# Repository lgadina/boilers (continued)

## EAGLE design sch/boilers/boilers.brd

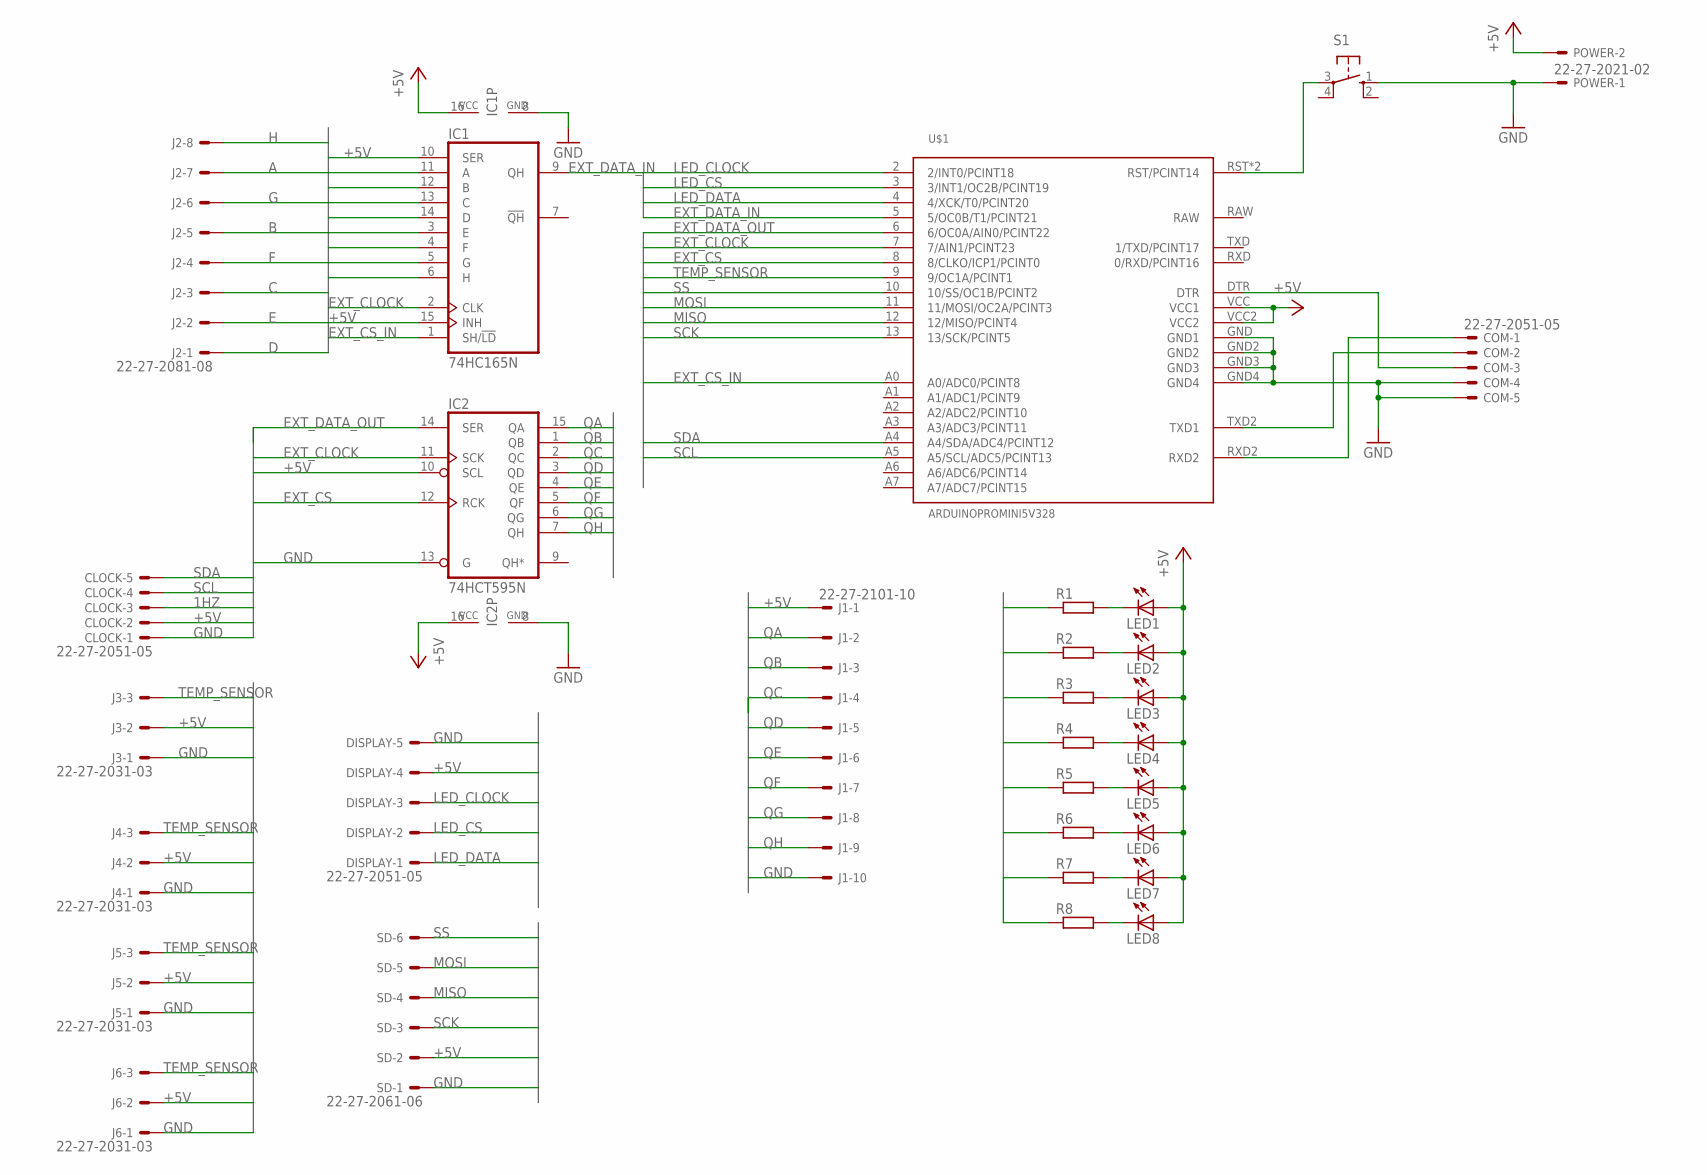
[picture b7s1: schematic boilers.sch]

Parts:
CLOCK: 22-27-2051-05; 6410-05
COM: 22-27-2051-05; 6410-05
DISPLAY: 22-27-2051-05; 6410-05
IC1: 74HC165N; DIL16
IC2: 74HCT595N; DIL16
J1: 22-27-2101-10; 6410-10
J2: 22-27-2081-08; 6410-08
J3, J4, J5, J6: 22-27-2031-03; 6410-03
LED1, LED2, LED3, LED4, LED5, LED6, LED7, LED8: LED5MM
POWER: 22-27-2021-02; 6410-02
R1, R2, R3, R4, R5, R6, R7, R8: R-EU_0207/10; 0207/10
S1: 10-XX; B3F-10XX
SD: 22-27-2061-06; 6410-06
U$1: ARDUINOPROMINI5V328; ARDUINOMINIPRO5V328

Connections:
1HZ: CLOCK.3
+5V: CLOCK.2, DISPLAY.4, IC1.10 (SER), IC1.15 (INH), IC1.16 (VCC), IC2.10 (SCL), IC2.16 (VCC), J1.1, J3.2, J4.2, J5.2, J6.2, LED1.A, LED2.A, LED3.A, LED4.A, LED5.A, LED6.A, LED7.A, LED8.A, POWER.2, SD.2, U$1.VCC (VCC1), U$1.VCC2
A: IC1.11 (A), J2.7
B: IC1.12 (B), J2.5
C: IC1.13 (C), J2.3
D: IC1.14 (D), J2.1
E: IC1.3 (E), J2.2
EXT_CLOCK: IC1.2 (CLK), IC2.11 (SCK), U$1.7 (7/AIN1/PCINT23)
EXT_CS: IC2.12 (RCK), U$1.8 (8/CLKO/ICP1/PCINT0)
EXT_CS_IN: IC1.1 (SH/!LD), U$1.A0 (A0/ADC0/PCINT8)
EXT_DATA_IN: IC1.9 (QH), U$1.5 (5/OC0B/T1/PCINT21)
EXT_DATA_OUT: IC2.14 (SER), U$1.6 (6/OC0A/AIN0/PCINT22)
F: IC1.4 (F), J2.4
G: IC1.5 (G), J2.6
GND: CLOCK.1, COM.4, COM.5, DISPLAY.5, IC1.8 (GND), IC2.8 (GND), IC2.13 (G), J1.10, J3.1, J4.1, J5.1, J6.1, POWER.1, S1.1 (S), SD.1, U$1.GND (GND1), U$1.GND2, U$1.GND3, U$1.GND4
H: IC1.6 (H), J2.8
LED_CLOCK: DISPLAY.3, U$1.2 (2/INT0/PCINT18)
LED_CS: DISPLAY.2, U$1.3 (3/INT1/OC2B/PCINT19)
LED_DATA: DISPLAY.1, U$1.4 (4/XCK/T0/PCINT20)
MISO: SD.4, U$1.12 (12/MISO/PCINT4)
MOSI: SD.5, U$1.11 (11/MOSI/OC2A/PCINT3)
unnamed: COM.1, U$1.RXD2
unnamed: COM.3, U$1.DTR
unnamed: LED1.K (C), R1.2
unnamed: LED2.K (C), R2.2
unnamed: LED3.K (C), R3.2
unnamed: LED4.K (C), R4.2
unnamed: LED5.K (C), R5.2
unnamed: LED6.K (C), R6.2
unnamed: LED7.K (C), R7.2
unnamed: LED8.K (C), R8.2
QA: IC2.15 (QA), J1.2, R1.1
QB: IC2.1 (QB), J1.3, R2.1
QC: IC2.2 (QC), J1.4, R3.1
QD: IC2.3 (QD), J1.5, R4.1
QE: IC2.4 (QE), J1.6, R5.1
QF: IC2.5 (QF), J1.7, R6.1
QG: IC2.6 (QG), J1.8, R7.1
QH: IC2.7 (QH), J1.9, R8.1
RESET: S1.3, U$1.RST (RST/PCINT14), U$1.RST2 (RST/PCINT14)
SCK: SD.3, U$1.13 (13/SCK/PCINT5)
SCL: CLOCK.4, U$1.A5 (A5/SCL/ADC5/PCINT13)
SDA: CLOCK.5, U$1.A4 (A4/SDA/ADC4/PCINT12)
SS: SD.6, U$1.10 (10/SS/OC1B/PCINT2)
TEMP_SENSOR: J3.3, J4.3, J5.3, J6.3, U$1.9 (9/OC1A/PCINT1)
TXD: COM.2, U$1.TXD2 (TXD1)

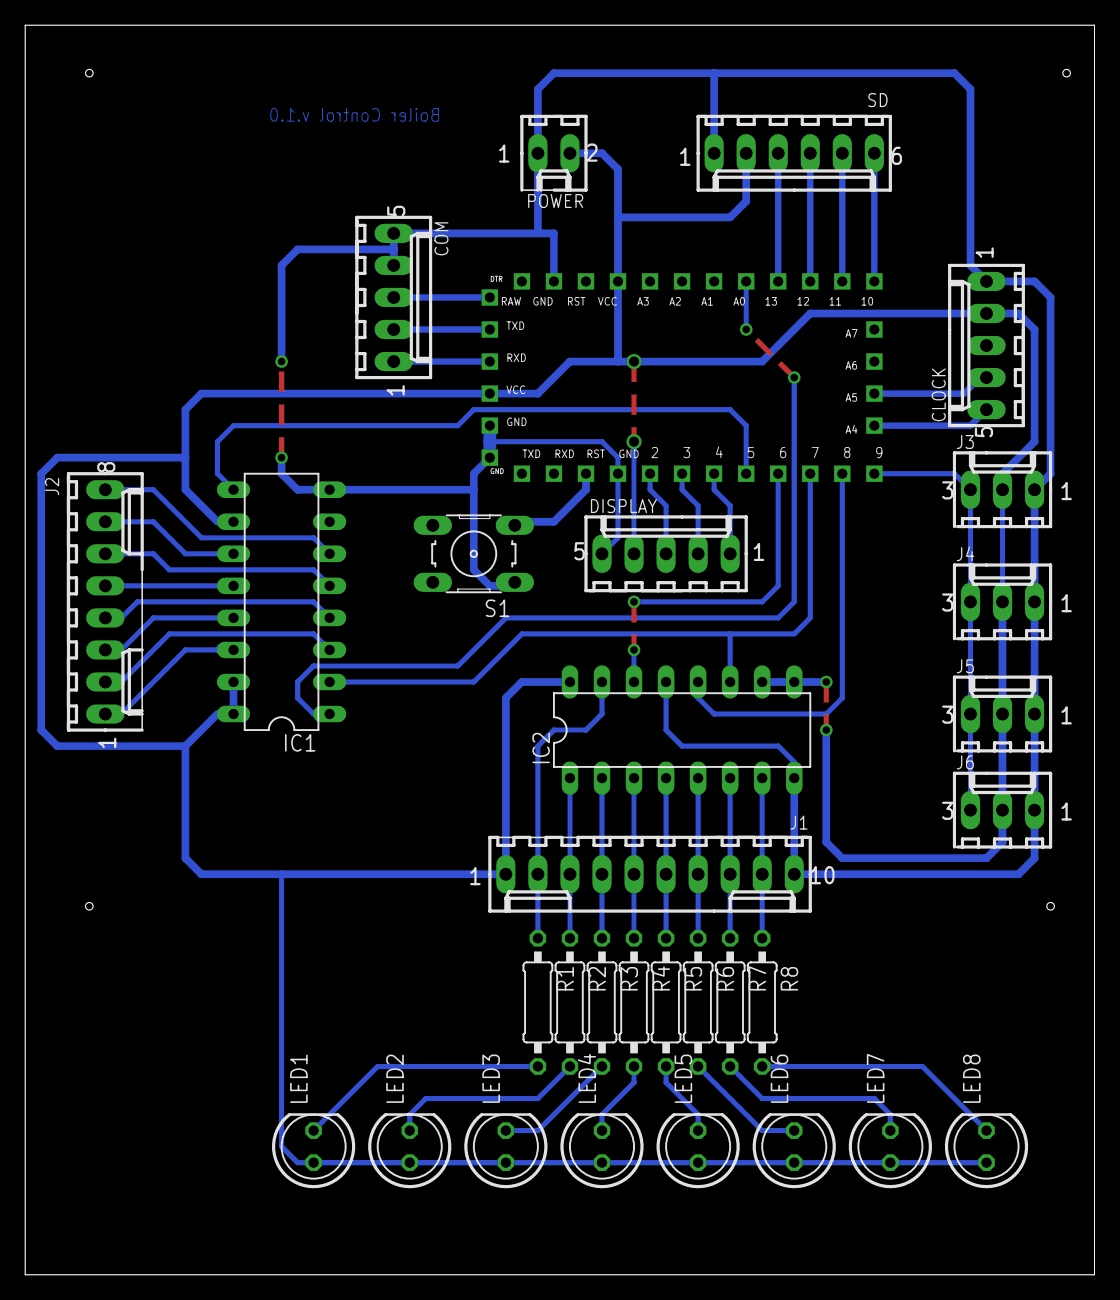
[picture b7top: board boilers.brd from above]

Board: 2 copper layers, 84.8 x 99.1 mm, 31 parts (0 on the bottom side), 45 nets.

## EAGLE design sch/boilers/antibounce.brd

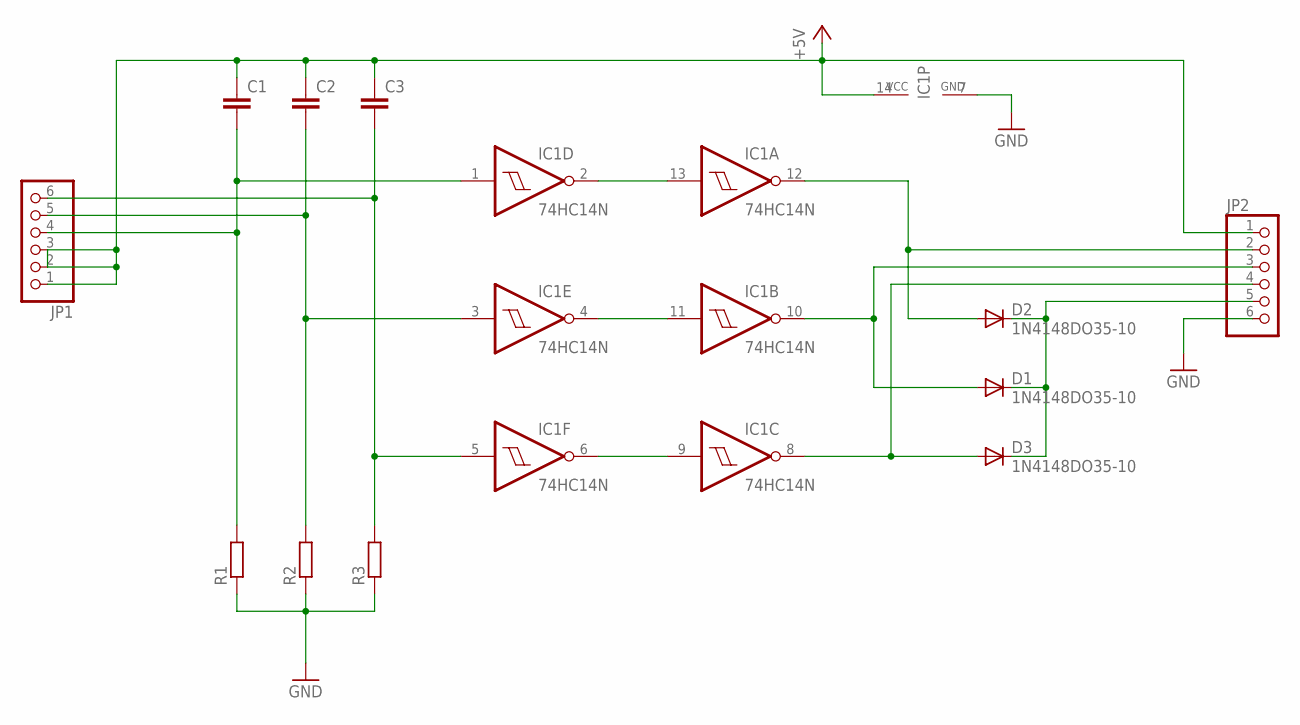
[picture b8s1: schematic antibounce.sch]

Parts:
C1, C2, C3: C-EU050-024X044; C050-024X044
D1, D2, D3: 1N4148DO35-10; DO35-10
IC1: 74HC14N; DIL14
JP1, JP2: PINHD-1X6; 1X06
R1, R2, R3: R-EU_0207/10; 0207/10

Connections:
+5V: C1.1, C2.1, C3.1, IC1.14 (VCC), JP1.1, JP1.2, JP1.3, JP2.1
GND: IC1.7 (GND), JP2.6, R1.1, R2.1, R3.1
unnamed: C1.2, IC1.1 (I), JP1.4, R1.2
unnamed: C2.2, IC1.3 (I), JP1.5, R2.2
unnamed: C3.2, IC1.5 (I), JP1.6, R3.2
unnamed: IC1.2 (O), IC1.13 (I)
unnamed: IC1.6 (O), IC1.9 (I)
unnamed: IC1.4 (O), IC1.11 (I)
unnamed: D2.A, IC1.12 (O), JP2.2
unnamed: D1.C, D2.C, D3.C, JP2.5
unnamed: D1.A, IC1.10 (O), JP2.3
unnamed: D3.A, IC1.8 (O), JP2.4

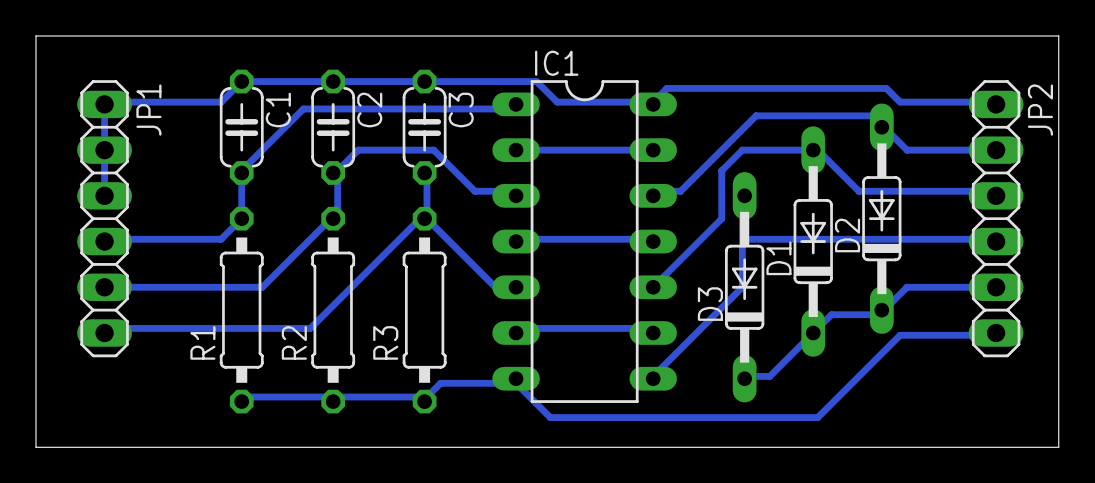
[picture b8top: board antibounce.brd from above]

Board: 2 copper layers, 56.8 x 22.9 mm, 12 parts (0 on the bottom side), 12 nets.

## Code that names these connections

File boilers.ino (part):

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
// занятые ноги
#define A0P 15
#define EXT_CS_IN 14
// 13
// 12
// 11
#define SD_CS_PIN 10
#define TEMP_SENSOR_PIN 9
#define BOILER_RELAY EXT_OUT_1
#define PUMP_RELAY EXT_OUT_2
#define EXT_CS 8
#define EXT_CLOCK 7
#define EXT_DATA_OUT 6
#define EXT_DATA_IN 5
#define LED_DATA_PIN 4 //MOSI
#define LED_CS_PIN 3   //CS
#define LED_CLOCK_PIN 2 //CLK


#define TX 1
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const char cminus = '-';
const char cstar = '*';

OneWire  ds(TEMP_SENSOR_PIN);  // on pin 10 (a 4.7K resistor is necessary)
LedControl lc=LedControl(LED_DATA_PIN, LED_CLOCK_PIN, LED_CS_PIN, 3);

#ifdef USE_RTC
RTC_DS1307 rtc;
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				memcpy(temp_sensor[k].addr, addr, sizeof(addr));
				temp_sensor[k].disp = cTempDisplay[k];
				temp_sensor[k].flags = TS_ON | type_s;
				temp_sensor[k].temp[2] = 0;
				ds.select(temp_sensor[k].addr);
				ds.write(0x4E);
				ds.write(temp_config);
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	
#ifdef FAST_PORT
	setup_pc_pwm_any();
	pinModeFast(EXT_CS_IN, OUTPUT);
	pinModeFast(EXT_DATA_IN, INPUT);
	pinModeFast(EXT_CS, OUTPUT);	
	pinModeFast(EXT_CLOCK, OUTPUT);
	pinModeFast(EXT_DATA_OUT, OUTPUT);	
	digitalWriteFast(EXT_CS_IN, HIGH);
	digitalWriteFast(EXT_CS, HIGH);
#else	
	pinMode(EXT_CS_IN, OUTPUT);	
	pinMode(EXT_DATA_IN, INPUT);
	pinMode(EXT_CS, OUTPUT);	
	pinMode(EXT_CLOCK, OUTPUT);
	pinMode(EXT_DATA_OUT, OUTPUT);	
	digitalWrite(EXT_CS_IN, HIGH);
	digitalWrite(EXT_CS, HIGH);
#endif	
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
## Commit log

2014-12-23 first
2014-12-27 220v
2014-12-27 antibounce
2014-12-27 On branch master
2014-12-27 v.1.0
2015-01-09 commutator
2015-01-10 display
2015-01-20 log format:
2015-01-21 refactoring pcb
2015-01-24 2-й вариант
2015-10-04 Схема и плата контроллера уличного освещения
2015-10-04 Исходники для street_lamp_controller
2015-10-04 дополнительный выход
2015-10-04 proteus
2015-10-24 Новая версия прошивки для контроллера
2015-10-26 Поправлены слои в печатной плате
2016-05-24 ACMon
2016-05-24 IL300
2022-04-10 new ard lib
